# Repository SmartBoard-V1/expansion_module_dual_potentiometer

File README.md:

# Dual Potentiometer Module with ATtiny48 and MCP3202 ADC

## Overview
This repository contains the design and implementation details of a Dual Potentiometer Module, integrating two distinct potentiometers with an MCP3202 ADC for precise analog-to-digital conversion. Designed for smartboard system expansions, it connects via a single smartboard connector and supports precise parameter control for a wide range of applications.

## Key Features
- **Variable Resistance Potentiometer**: Smooth, continuous rotation from 0 to maximum resistance, suitable for volume or intensity control.
- **Center-Detent Potentiometer**: Features a tactile midpoint for easy balance or center-value setting, ideal for parameters requiring deviation from a central point (e.g., left-right, negative-positive adjustments).
- **MCP3202 ADC**: A 12-bit Analog-to-Digital Converter (ADC) with SPI interface for high precision analog signal conversion, enhancing the module's accuracy and reliability.
- **SPI Communication**: Facilitates robust and versatile communication through the Serial Peripheral Interface (SPI), ensuring reliable data transfer between the ADC and any connected smartboard system.
- **Smartboard Compatibility**: Easily integrates with smartboard systems through a dedicated connector.
- **Ease of Programming**: Direct programming and configuration via connector signals.

### MCP3202 ADC
The MCP3202 ADC is an integral part of this module, offering high-resolution, 12-bit analog-to-digital conversion. It features two analog input channels, perfect for reading the positions of the potentiometers. The ADC communicates via SPI, ensuring accurate and swift data transfer for real-time adjustments. Detailed information about the MCP3202 ADC can be found in the [documentation](media/21034F-64776.pdf).

### Schematic and Board Design

*The schematic provides a comprehensive view of the circuit design, illustrating the integration of the potentiometers, ATtiny48 microcontroller, and MCP3202 ADC.*

*This image shows the PCB layout, highlighting the placement of components such as the potentiometers, ATtiny48, and MCP3202 ADC, giving a clear overview of the design.*

## Contributions and Feedback
Contributions to this project are welcome. If you have improvement suggestions or have developed new features, please fork the repository, implement your changes, and submit a pull request. For questions or issues, feel free to open an issue in the GitHub repository.

## License
This project is licensed under the MIT License. You are free to use, modify, and distribute this design in both private and commercial settings. Attribution to the original author, Adam Łuczak, is appreciated but not required. The project is provided "as is", without warranty of any kind.

For the complete terms, please refer to the MIT License documentation.

## Contact
For inquiries or suggestions regarding this project, please contact Adam Łuczak at adam.luczak@outlook.com.

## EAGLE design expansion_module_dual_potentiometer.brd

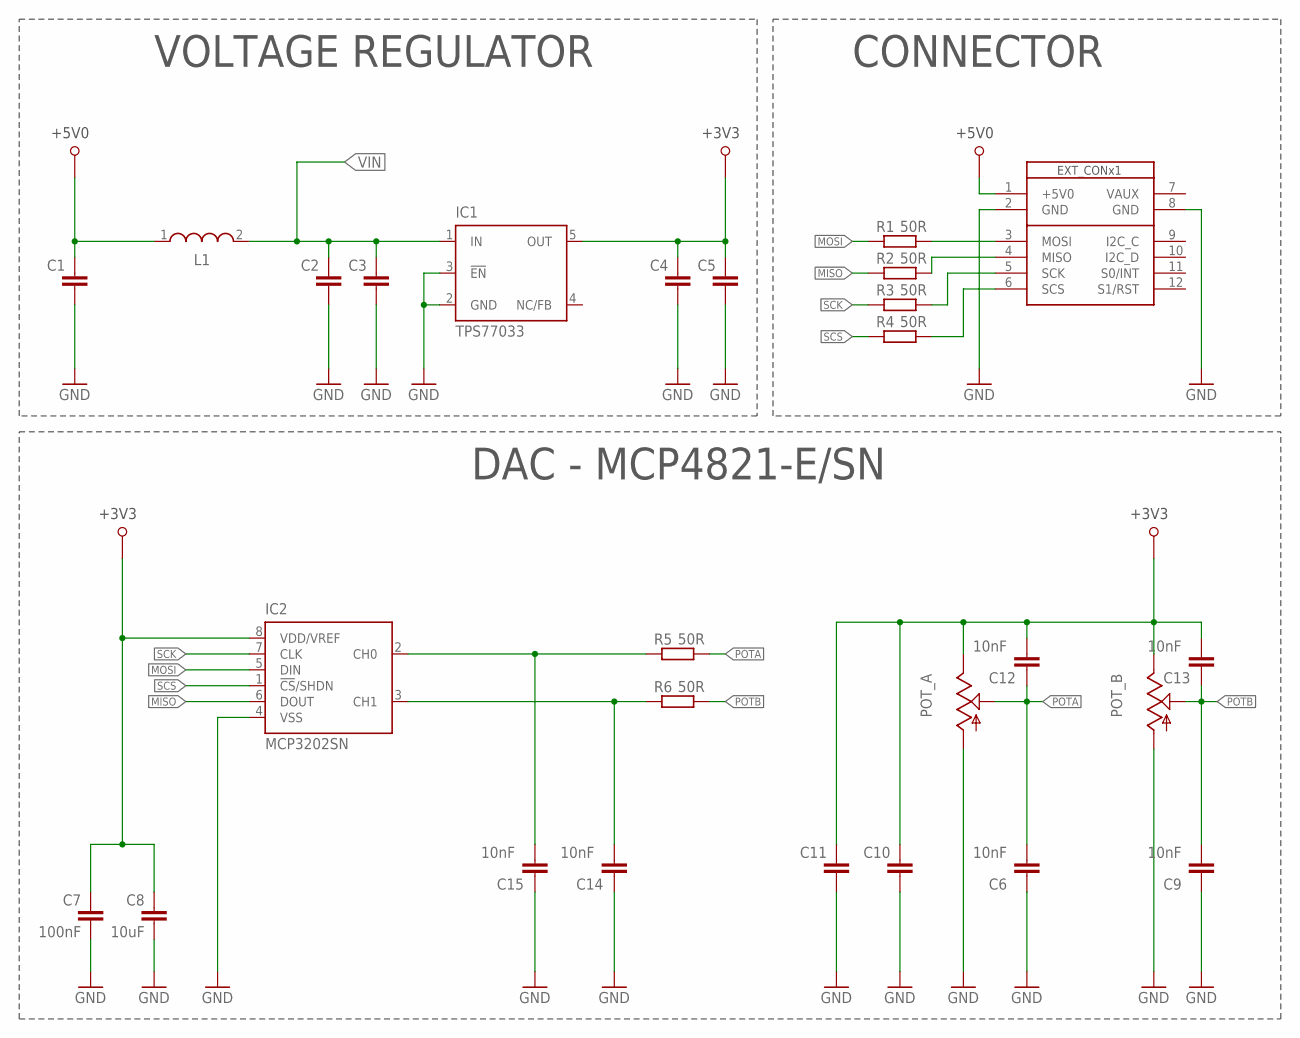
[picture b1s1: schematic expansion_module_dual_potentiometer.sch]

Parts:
C1, C2, C3, C4, C5, C10, C11: C-EUC0805; C0805
C6, C9, C12, C13, C14, C15: 10nF; C0805
C7: 100nF; C0805
C8: 10uF; C0805
IC1: TPS77033; SOT23-DBV
IC2: MCP3202SN; SO-08
L1: WE-LQ_1210; WE-LQ_M
POT_A: 9MM_SNAP-IN_POT_; 9MM_SNAP-IN_POT
POT_B: 9MM_SNAP-IN_POT_; 9MM_SNAP-IN_POT
R1, R2, R3, R4, R5, R6: 50R; R0805
U$1: SB_EXT_CON_X1_SPI; SB_EXT_CON_X1_FULL

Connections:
+3V3: C4.2, C5.2, C7.2, C8.2, C10.2, C11.2, C12.1, C13.1, IC1.5 (OUT), IC2.8 (VDD/VREF), POT_A.3 (E), POT_B.3 (E)
+5V0: C1.2, L1.1, U$1.1 (+5V0)
GND: C1.1, C2.1, C3.1, C4.1, C5.1, C6.2, C7.1, C8.1, C9.2, C10.1, C11.1, C14.2, C15.2, IC1.2 (GND), IC1.3 (!EN), IC2.4 (VSS), POT_A.1 (A), POT_B.1 (A), U$1.2 (GND), U$1.8 (GND)
MISO: IC2.6 (DOUT), R2.1
MOSI: IC2.5 (DIN), R1.1
unnamed: R1.2, U$1.3 (MOSI)
unnamed: R3.2, U$1.5 (SCK)
unnamed: R4.2, U$1.6 (SCS)
unnamed: R2.2, U$1.4 (MISO)
unnamed: C14.1, IC2.3 (CH1), R6.1
unnamed: C15.1, IC2.2 (CH0), R5.1
POTA: C6.1, C12.2, POT_A.2 (S), R5.2
POTB: C9.1, C13.2, POT_B.2 (S), R6.2
SCK: IC2.7 (CLK), R3.1
SCS: IC2.1 (!CS!/SHDN), R4.1
VIN: C2.2, C3.2, IC1.1 (IN), L1.2

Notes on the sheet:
CONNECTOR
VOLTAGE REGULATOR
DAC - MCP4821-E/SN

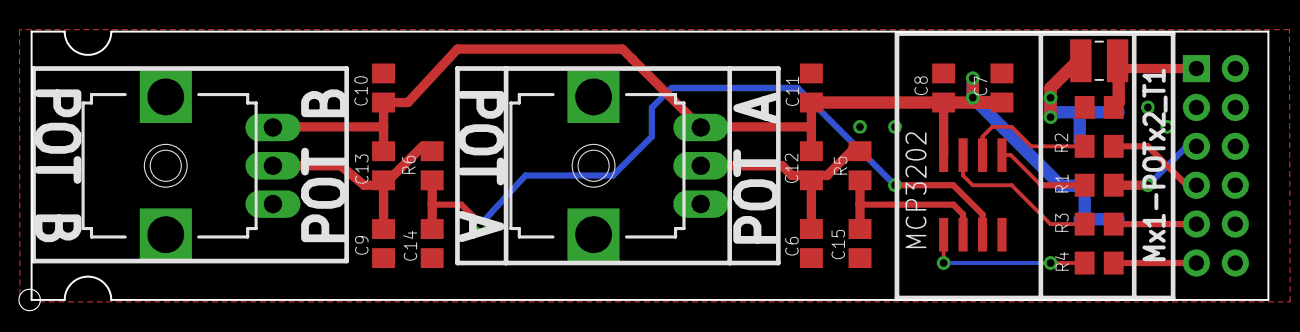
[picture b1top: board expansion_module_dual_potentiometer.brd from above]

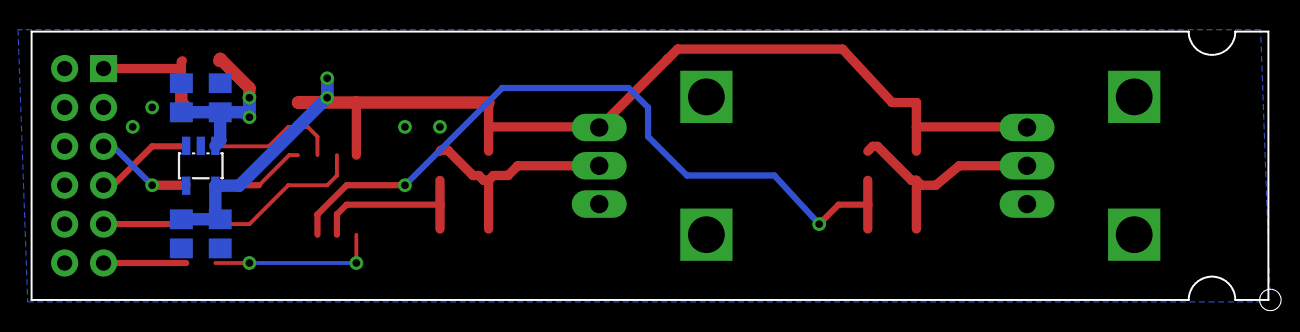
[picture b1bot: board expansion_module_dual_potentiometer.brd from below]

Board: 2 copper layers, 80.8 x 17.5 mm, 27 parts (5 on the bottom side), 16 nets.

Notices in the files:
README.md:
License: MIT
parts and their libraries:
EagleLibrary_Wuerth_Elektronik_eiSos_rev: Copyright: Würth Elektronik
